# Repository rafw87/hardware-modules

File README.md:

# Various hardware modules

## [esp-prog-adapter](esp-prog-adapter)

Simple adapter allowing to connect [ESP-PROG board](https://docs.espressif.com/projects/espressif-esp-iot-solution/en/latest/hw-reference/ESP-Prog_guide.html)
to breadboard, using provided IDC cables (1.27mm pitch).

## [ESP-32 board on Arduino footprint](modules/esp-32-board)

ESP-WROOM-32 (or ESP32-SOLO-1) development kit with Micro-USB port, DC Input and ESP-PROG interface,
based on Arduino footprint.

## [NE555 Astable Circuit Breadboard Adapter](modules/ne555-astable-adapter)

This adapter implements common wiring for NE555 astable circuit, exposing pins for external R1, R2 and C1, and of course for VCC, GND and output.

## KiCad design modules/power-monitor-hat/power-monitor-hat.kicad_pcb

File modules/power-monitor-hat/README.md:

# Power monitor HAT

Turns your Raspberry PI into 3-channel voltage and current monitor for other devices.

## Features
 - 3 separate channels, each with own INA219 chip and shunt resistor (see below for resistor selection)
 - Different possible power sources (controlled by jumpers):
   - external (separate input for each channel), provided on screw terminal,
   - internal 5V from common DC input
     - may be shorted to Raspberry's 5V pin using solderjumper on the bottom or left as separate circuit,
   - internal 3.3V - powered from 5V using internal LDO regulator
 - Fuse and an "ideal diode" circuit protecting DC source when shorted.
 - 4 LEDs:
   - PWR (connected to 5V bus)
   - 3 LEDs, one for each channel, connected to selected channel's power source
 - Header for UART - to communicate with measured device
 - Test points for I2C
 - Standard ID EEPROM from [hat specification](https://github.com/raspberrypi/hats)
 
## Devices list

### I2C
 Address | Device   | Description 
:-------:|:--------:|:-----------:
|  0x40  |  INA219  | Channel 1  
|  0x41  |  INA219  | Channel 2  
|  0x42  |  INA219  | Channel 3  

## Shunt resistor selection

Equations and tables below may help to select proper shunt resistor according to needs.

### Current

$R_{shunt}$ | Absolute maximum current* | Maximum measurable current** | Maximum recommended current**
:----------:|:-------------------------:|:----------------------------:|:-----------------------------:
|  0.1Ω     | 2.73A / 3.16A             | 3.20A                        | 0.40A
|  0.2Ω     | 1.93A / 2.23A               | 1.60A                        | 0.20A
|  0.5Ω     | 1.22A / 1.41A               | 0.64A                        | 0.08A
|  1.0Ω     | 0.86A / 1.00A               | 0.32A                        | 0.04A

\* Maximum allowed current for (respecively) 0.75W and 1W rated resistor of given resistance. Remember to include some margin for safety purpose. Equation:
  $$I = \sqrt{P_{max} \over R_{shunt}}$$

\** Maximum measurable ( $PGA = /8$, $V_{pga} = \pm 320mV$ ) and recommended ( $PGA = 1$, $V_{pga} = \pm 40mV$ ) current for given resistor. Equation:
  $$I = {V_{pga} \over R_{shunt}}$$

### Voltage drop

$R_{shunt}$       | 0.1A  | 0.2A  | 0.5A  | 1A     | 2A
:----------------:|:-----:|:-----:|:-----:|:------:|:----:
|  0.1Ω           | 0.01V | 0.02V | 0.05V | 0.10V  | 0.20V
|  0.2Ω           | 0.02V | 0.04V | 0.10V | 0.20V  | 0.40V
|  0.5Ω           | 0.05V | 0.10V | 0.25V | 0.50V  | 1.00V
|  1.0Ω           | 0.10V | 0.20V | 0.50V | 1.00V  | 2.00V

Equation:
$$V_{shunt} = R_{shunt} * I$$

### Tolerance and temperature coefficient
Simple answer: less is better (but more expensive) :)

Depends on actual purpose of HAT and expected quality of measurements.

Current measurement tolerance is linear to resistor tolerance, so for 1% tolerance we can expect also 1% variation of current measurement.

Due of temperature coefficient, it's also recommended to not "stress" resistor close to its maximum power rating, causing excessive heating.
Some heat is unfortunately generated by RaspberryPI itself. If needed, it may be compensated programmatically (knowing temperature coefficient and actual temperature) or HAT may be connected using extension cable to not be affected by RPi's heat.

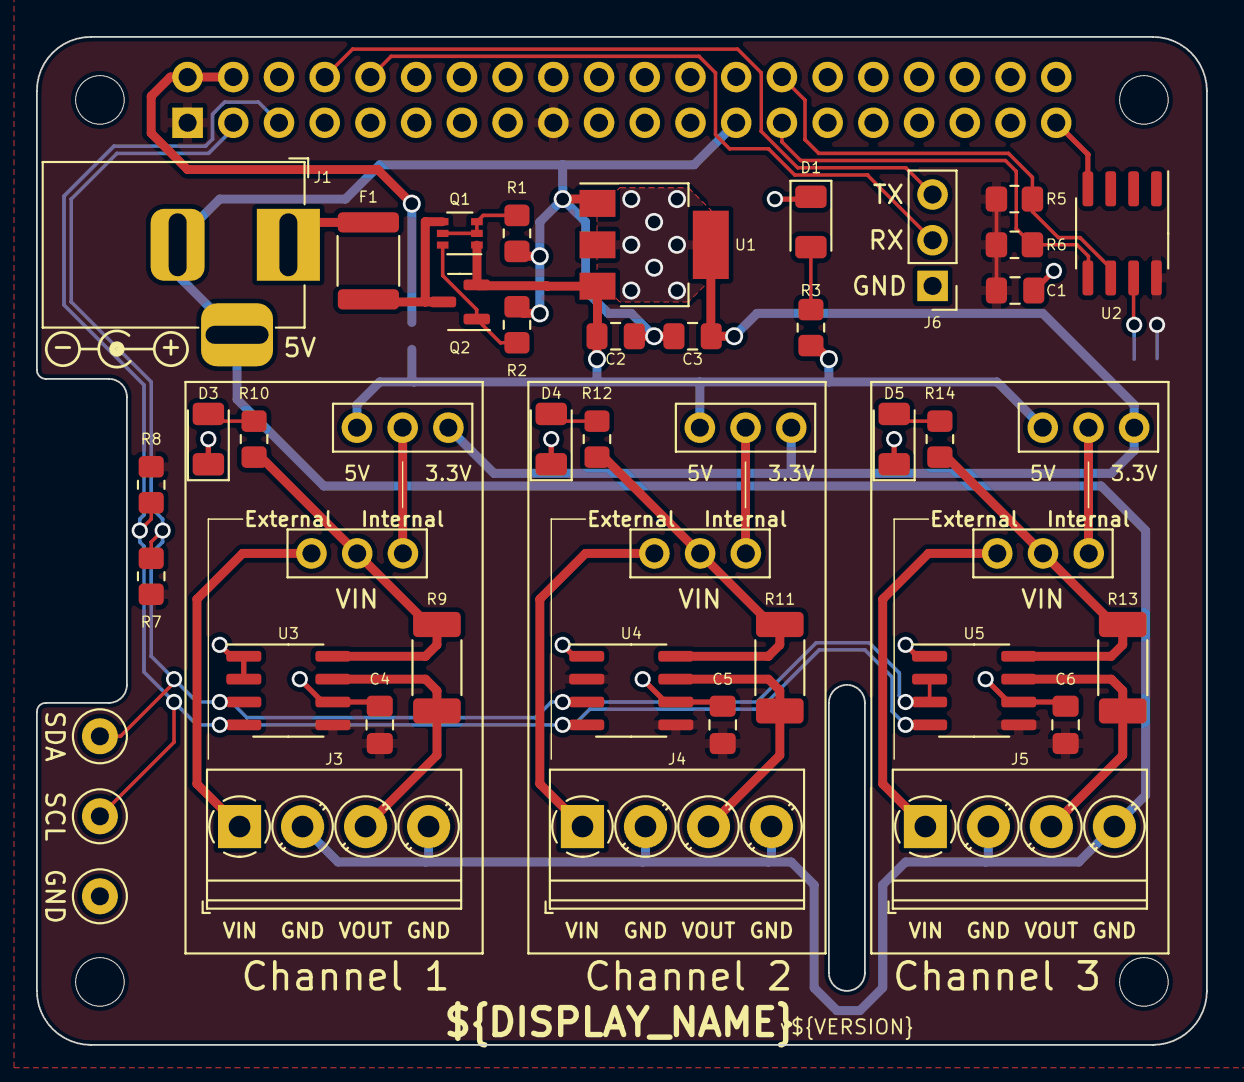
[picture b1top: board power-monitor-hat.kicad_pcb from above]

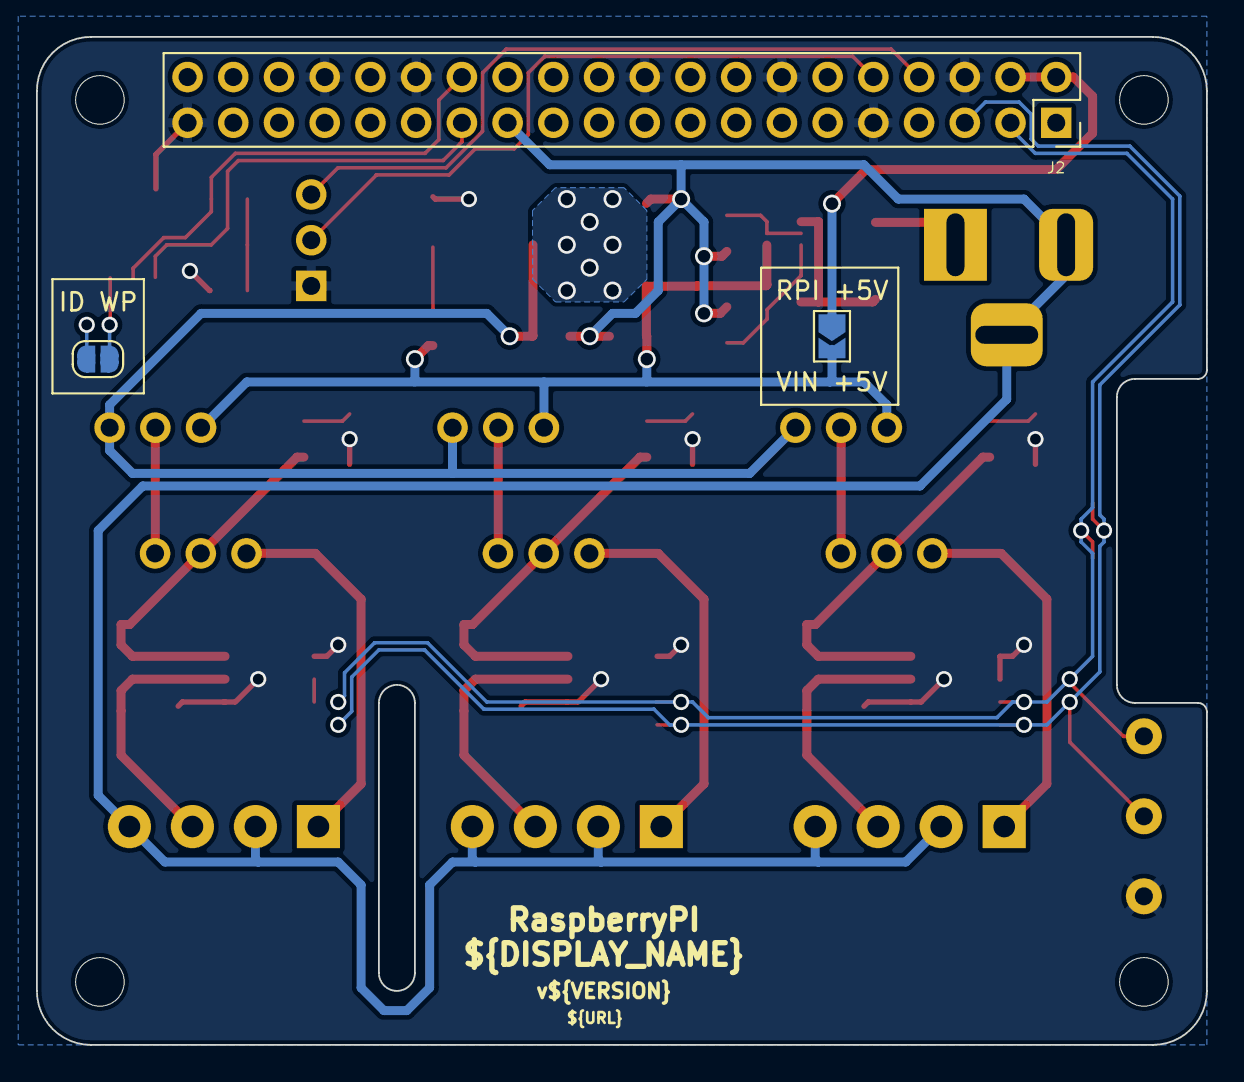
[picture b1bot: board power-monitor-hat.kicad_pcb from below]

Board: 2 copper layers, 65.0 x 56.0 mm, 53 parts (3 on the bottom side), 33 nets.

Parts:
C1, C4, C5, C6: 100n; C_0805_2012Metric_Pad1.18x1.45mm_HandSolder
C2, C3: 10u; C_0805_2012Metric_Pad1.18x1.45mm_HandSolder
D1, D3, D4, D5: LED; LED_1206_3216Metric
F1: MF-MSMF250/16X-2; Fuse_1812_4532Metric
J1: Barrel_Jack_Switch; BarrelJack_CLIFF_FC68148_Horizontal
J2: GPIO; PinSocket_2x20_P2.54mm_Vertical
J3, J4, J5: OutputTerminal; TerminalBlock_Phoenix_PT-1,5-4-3.5-H_1x04_P3.50mm_Horizontal
J6: Conn_01x03; PinHeader_1x03_P2.54mm_Vertical
JP1: 5V_Bridge; SolderJumper-2_P1.3mm_Open_TrianglePad1.0x1.5mm
JP2: ID_WP; SolderJumper-2_P1.3mm_Open_RoundedPad1.0x1.5mm
JP3, JP4, JP5, JP6, JP7, JP8: Jumper; PinHeader_1x03_P2.54mm_Vertical_NoFP
MH1, MH2, MH3, MH4: MountingHole_2.7mm_M2.5
Q1: BC856BDW1; SOT-363_SC-70-6
Q2: SI2301CDS; SOT-23
R1, R7, R8: 10k; R_0805_2012Metric_Pad1.20x1.40mm_HandSolder
R2: 47k; R_0805_2012Metric_Pad1.20x1.40mm_HandSolder
R3: 470R; R_0805_2012Metric_Pad1.20x1.40mm_HandSolder
R5, R6: 3.9k; R_0805_2012Metric_Pad1.20x1.40mm_HandSolder
R9, R11, R13: 0R5; R_2010_5025Metric_Pad1.40x2.65mm_HandSolder
R10, R12, R14: 2kR; R_0805_2012Metric_Pad1.20x1.40mm_HandSolder
SYM1: Symbol_Barrel_Polarity
TP1, TP2, TP3: TestPoint; TestPoint_Loop_D1.80mm_Drill1.0mm_Beaded
U1: NCP1117-3.3_SOT223; SOT-223-3_TabPin2
U2: CAT24C256; SOIC-8_3.9x4.9mm_P1.27mm
U3, U4, U5: INA219AxD; SOIC-8_3.9x4.9mm_P1.27mm

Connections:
+3.3V: C1.1, C4.1, C5.1, C6.1, J2.1 (3V3), J2.17 (3V3), JP2.2 (B), R5.1, R6.1, R7.1, R8.1, U2.8 (VCC), U3.5 (VS), U4.2 (A0), U4.5 (VS), U5.5 (VS)
+3.3VP: C3.1, JP4.3 (B), JP6.3 (B), JP8.3 (B), U1.2 (VO)
+5V: J2.2 (5V), J2.4 (5V), JP1.1 (A)
+5VP: C2.1, JP1.2 (B), JP4.1 (A), JP6.1 (A), JP8.1 (A), Q1.1 (E1), Q2.2 (S), R3.2, U1.3 (VI)
/ID_SCL: J2.28 (ID_SC/GPIO1), R5.2, U2.6 (SCL)
/ID_SDA: J2.27 (ID_SD/GPIO0), R6.2, U2.5 (SDA)
/PowerChannel 1/EXTERNAL_VIN: J3.1, JP3.1 (A)
/PowerChannel 1/INTERNAL_VIN: JP3.3 (B), JP4.2 (C)
/PowerChannel 1/VIN: JP3.2 (C), R9.1, R10.2, U3.8 (IN+)
/PowerChannel 1/VOUT: J3.3, R9.2, U3.7 (IN-)
/PowerChannel 2/EXTERNAL_VIN: J4.1, JP5.1 (A)
/PowerChannel 2/INTERNAL_VIN: JP5.3 (B), JP6.2 (C)
/PowerChannel 2/VIN: JP5.2 (C), R11.1, R12.2, U4.8 (IN+)
/PowerChannel 2/VOUT: J4.3, R11.2, U4.7 (IN-)
/PowerChannel 3/EXTERNAL_VIN: J5.1, JP7.1 (A)
/PowerChannel 3/INTERNAL_VIN: JP7.3 (B), JP8.2 (C)
/PowerChannel 3/VIN: JP7.2 (C), R13.1, R14.2, U5.8 (IN+)
/PowerChannel 3/VOUT: J5.3, R13.2, U5.7 (IN-)
/RX: J2.10 (GPIO15/RXD), J6.2
/SCL: J2.5 (SCL/GPIO3), R8.2, TP3.1, U3.4 (SCL), U4.4 (SCL), U5.4 (SCL)
/SDA: J2.3 (SDA/GPIO2), R7.2, TP2.1, U3.3 (SDA), U4.3 (SDA), U5.2 (A0), U5.3 (SDA)
/TX: J2.8 (GPIO14/TXD), J6.3
/Vfused: F1.2, Q1.4 (E2), Q2.3 (D)
/Vpsu: F1.1, J1.1
GND: C1.2, C4.2, C5.2, C6.2, D1.1 (K), D3.1 (K), D4.1 (K), D5.1 (K), J2.6 (GND), J2.9 (GND), J2.14 (GND), J2.20 (GND), J2.30 (GND), J2.34 (GND), J2.39 (GND), J6.1, TP1.1, U2.4 (GND), U3.1 (A1), U3.2 (A0), U3.6 (GND), U4.1 (A1), U4.6 (GND), U5.1 (A1), U5.6 (GND)
GNDPWR: C2.2, C3.2, J1.2, J1.3, J2.25 (GND), J3.2, J3.4, J4.2, J4.4, J5.2, J5.4, R1.2, R2.2, U1.1 (GND)
unnamed: D1.2 (A), R3.1
unnamed: JP2.1 (A), U2.7 (WP)
unnamed: Q1.2 (B1), Q1.3 (C2), Q1.5 (B2), R1.1
unnamed: Q1.6 (C1), Q2.1 (G), R2.1
unnamed: D3.2 (A), R10.1
unnamed: D4.2 (A), R12.1
unnamed: D5.2 (A), R14.1

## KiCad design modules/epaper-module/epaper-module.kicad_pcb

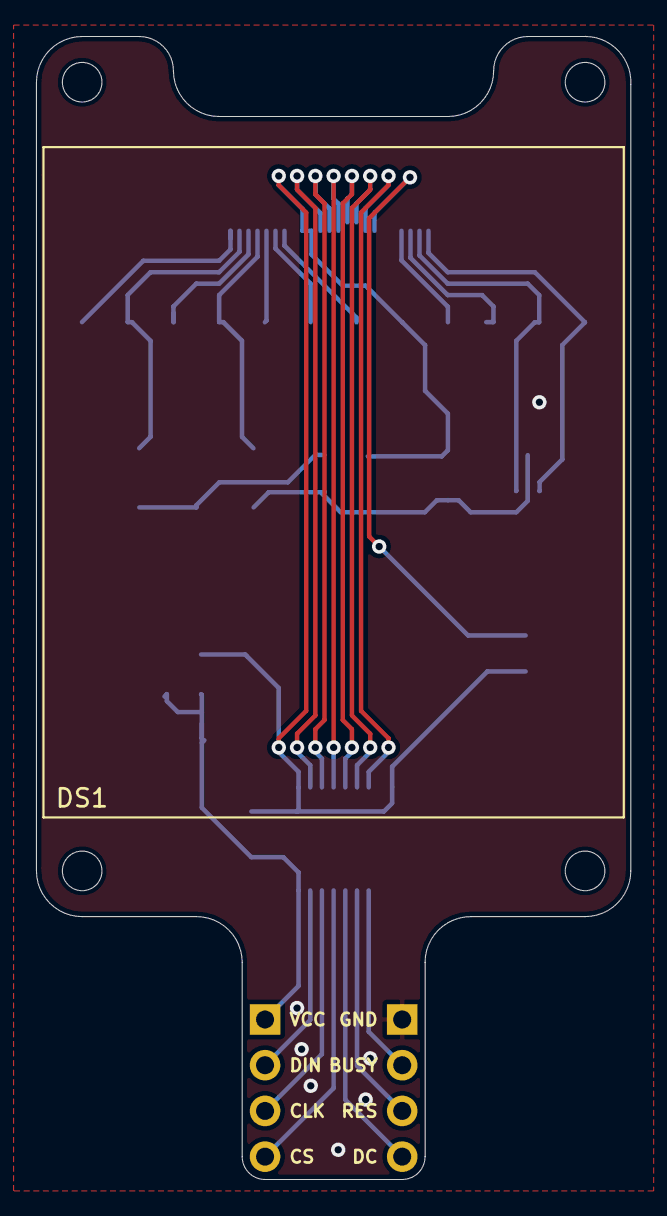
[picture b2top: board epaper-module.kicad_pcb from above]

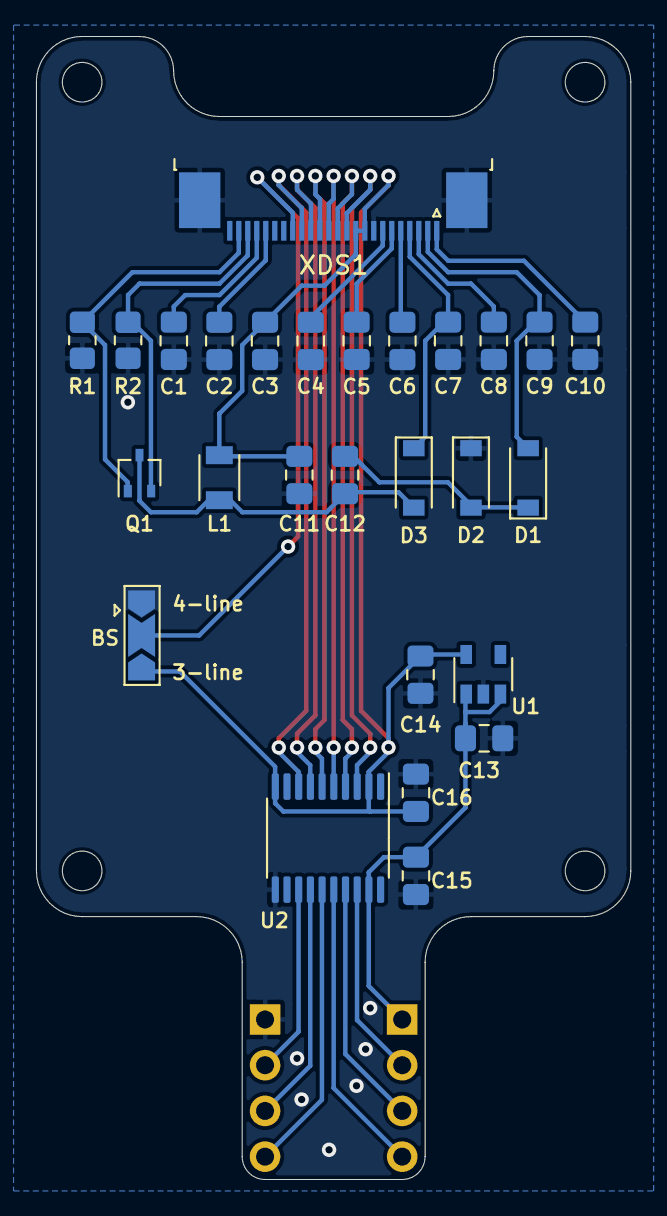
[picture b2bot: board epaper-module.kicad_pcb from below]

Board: 2 copper layers, 33.0 x 63.5 mm, 34 parts (29 on the bottom side), 29 nets.

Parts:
C1, C2, C3, C4, C5, C6, C7, C8, C9, C10: 1uF; C_0805_2012Metric_Pad1.18x1.45mm_HandSolder
C11, C12, C14: 4.7uF; C_0805_2012Metric_Pad1.18x1.45mm_HandSolder
C13: 10uF; C_0805_2012Metric_Pad1.18x1.45mm_HandSolder
C15, C16: 100nF; C_0805_2012Metric_Pad1.18x1.45mm_HandSolder
D1, D2, D3: MBR0530; D_SOD-123
DS1: WSH-12561
H1, H2, H3, H4: MountingHole; MountingHole_2.2mm_M2
J1, J2: Conn_01x04; PinHeader_1x04_P2.54mm_Vertical
JP1: Jumper_NC_Dual; SolderJumper-3_P2.0mm_Open_TrianglePad1.0x1.5mm
L1: 10uH; L_TDK_NLV25_2.5x2.0mm
Q1: Si1308EDL; SOT-323_SC-70
R1: 10k; R_0805_2012Metric_Pad1.20x1.40mm_HandSolder
R2: 3 Ohm; R_0805_2012Metric_Pad1.20x1.40mm_HandSolder
U1: MIC5504-3.3YM5; SOT-23-5
U2: TXS0108EPW; TSSOP-20_4.4x6.5mm_P0.65mm
XDS1: WSH-12561-FFC-MP; TE_2-1734839-4_1x24-1MP_P0.5mm_Horizontal

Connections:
+3V3: C3.1, C11.1, C14.1, C16.1, JP1.3, L1.2, U1.5, U2.2, U2.10, XDS1.9, XDS1.10
/BS: JP1.2, XDS1.17
/BUSY: J1.2, U2.13
/BUSY': U2.8, XDS1.16
/CLK: J2.3, U2.17
/CLK': U2.4, XDS1.12
/CS: J2.4, U2.16
/CS': U2.5, XDS1.13
/DC: J1.4, U2.15
/DC': U2.6, XDS1.14
/DIN: J2.2, U2.18
/DIN': U2.3, XDS1.11
/GDR: Q1.1, R1.1, XDS1.23
/PREVGH: C7.1, D3.1, XDS1.4
/PREVGL: C9.1, D1.2, XDS1.2
/RES: J1.3, U2.14
/RES': U2.7, XDS1.15
/RESE: Q1.2, R2.1, XDS1.22
/VCOM: C10.1, XDS1.1
/VDD: C4.1, XDS1.7
/VSH1: C6.1, XDS1.5
/VSH2: C2.1, XDS1.20
/VSL: C8.1, XDS1.3
GND: C1.2, C2.2, C3.2, C4.2, C5.2, C6.2, C7.2, C8.2, C9.2, C10.2, C11.2, C13.2, C14.2, C15.2, C16.2, D2.1, J1.1, JP1.1, R1.2, R2.2, U1.2, U2.11, XDS1.8, XDS1.MP
unnamed: C1.1, XDS1.21
unnamed: C5.1, XDS1.6
unnamed: C12.1, D1.1, D2.2
unnamed: C12.2, D3.2, L1.1, Q1.3
VCC: C13.1, C15.1, J2.1, U1.1, U1.3, U2.19

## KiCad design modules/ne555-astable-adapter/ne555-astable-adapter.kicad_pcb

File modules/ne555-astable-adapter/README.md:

# NE555 Astable Circuit Breadboard Adapter

## Story
OK, so you want to build a timer, emiting pulses with given interval on breadboard using NE555. Easy, right?
All you need is to put your NE555 in the middle and implement astable circuit around it, like this:

Looks easy? Only on the schematic :wink:
- Trigger and Treshold should be connected, but are on the opposite side, so single jumper is not an option.
  What is the shortest wire you have? :)
- R2 should connect pin 7 either with pin 2 (over IC?) or with pin 6 (requires vertical resistor).
- You need power and ground on both sides.
- Quickly you have no idea which pins are connected without looking into schematic :wink:

Finally you ends with something like this:

Maybe is there any easier way? :thinking: Maybe some adapter?

## Adapter

This adapter implements common wiring for NE555 astable circuit, exposing pins for external R1, R2 and C1,
and of course for VCC, GND and output. Additionally exposes pin for Control, but allows also to solder fixed C2 capacitor.
Some pins are duplicated, making it easier to connect and allowing to choose most comfortable pitch.

Comparison:

- Trigger and Treshold are internally connected and exposed as TRI
- Distance between R2 terminals can be 7.62mm, 10.16mm or 12.7mm (3, 4 or 5 holes on breadboard) making it easy to connect
  with horizontal resistor
- It's possible to connect to VCC/GND only from one side (as above)
- Pins are labelled

Adapter from top:

## Resources
- [Schematic](docs/ne555-astable-adapter-schematic.pdf?raw=true)
- [BOM](https://htmlpreview.github.io/?https://raw.githubusercontent.com/rafw87/hardware-modules/master/modules/ne555-astable-adapter/docs/ne555-astable-adapter-bom.html)
- [Project on PCBWay](https://www.pcbway.com/project/shareproject/NE555_Astable_Circuit_Breadboard_Adapter.html)
- Gerbers
  - [PCBWay](docs/gerbers/ne555-astable-adapter-PCBWay.zip?raw=true)

## License
<br />This work is licensed under a <a rel="license" href="http://creativecommons.org/licenses/by-sa/4.0/">Creative Commons Attribution-ShareAlike 4.0 International License</a>.

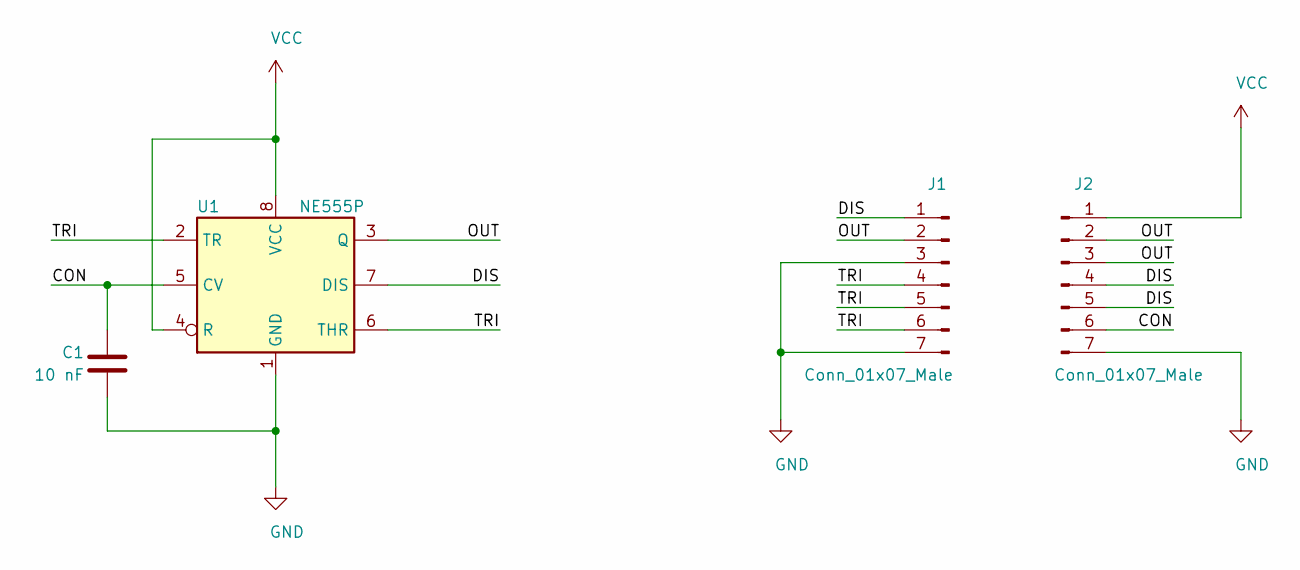
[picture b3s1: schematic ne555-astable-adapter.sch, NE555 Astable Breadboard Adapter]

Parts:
C1: 10 nF; C_Disc_D3.0mm_W1.6mm_P2.50mm
J1, J2: Conn_01x07_Male; PinHeader_1x07_P2.54mm_Vertical
U1: NE555P; DIP-8_W7.62mm

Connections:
/CON: C1.1, J2.6, U1.5 (CV)
/DIS: J1.1, J2.4, J2.5, U1.7 (DIS)
/OUT: J1.2, J2.2, J2.3, U1.3 (Q)
/TRI: J1.4, J1.5, J1.6, U1.2 (TR), U1.6 (THR)
GND: C1.2, J1.3, J1.7, J2.7, U1.1 (GND)
VCC: J2.1, U1.4 (R), U1.8 (VCC)

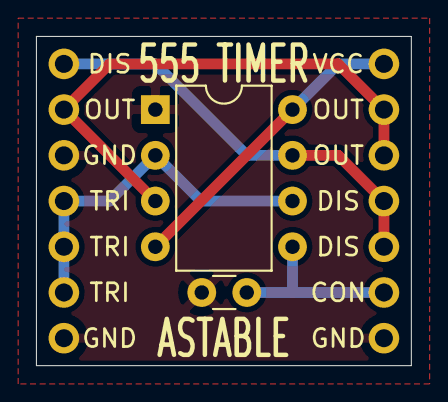
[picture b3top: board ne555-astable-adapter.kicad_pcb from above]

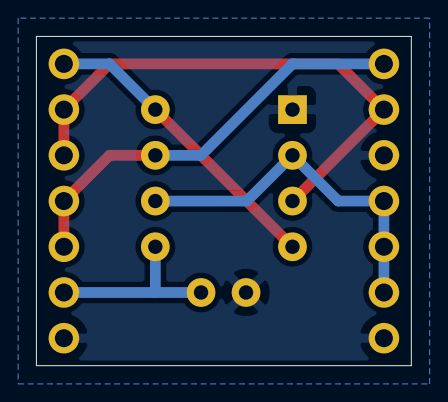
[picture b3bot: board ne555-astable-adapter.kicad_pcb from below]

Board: 2 copper layers, 20.8 x 18.3 mm, 4 parts (2 on the bottom side), 6 nets.

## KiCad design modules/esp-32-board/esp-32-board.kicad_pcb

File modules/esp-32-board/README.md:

# ESP-32 board on Arduino footprint

ESP-WROOM-32 (or ESP32-SOLO-1) development kit with Micro-USB port, DC Input and ESP-PROG interface.

Based on Arduino Uno/Leonardo footprint, so (apart from interesting appearance)
allows to use stands and (partially) enclosures from original Arduino.

**Note:** It's not an Arduino clone, so it's not compatible (neither electrically nor physically) with Arduino shields.
Functionally it's evaluation board like ESP32-DevKitC.

## Resources
- [Schematic](docs/esp-32-board-schematic.pdf?raw=true)
- [BOM](https://htmlpreview.github.io/?https://raw.githubusercontent.com/rafw87/hardware-modules/master/modules/esp-32-board/docs/esp-32-board-bom.html)
- [Project on PCBWay](https://www.pcbway.com/project/shareproject/ESP_32_board_on_Arduino_footprint.html)
- Gerbers
  - [PCBWay](docs/gerbers/esp-32-board-PCBWay.zip?raw=true)

## License
<br />This work is licensed under a <a rel="license" href="http://creativecommons.org/licenses/by-sa/4.0/">Creative Commons Attribution-ShareAlike 4.0 International License</a>.

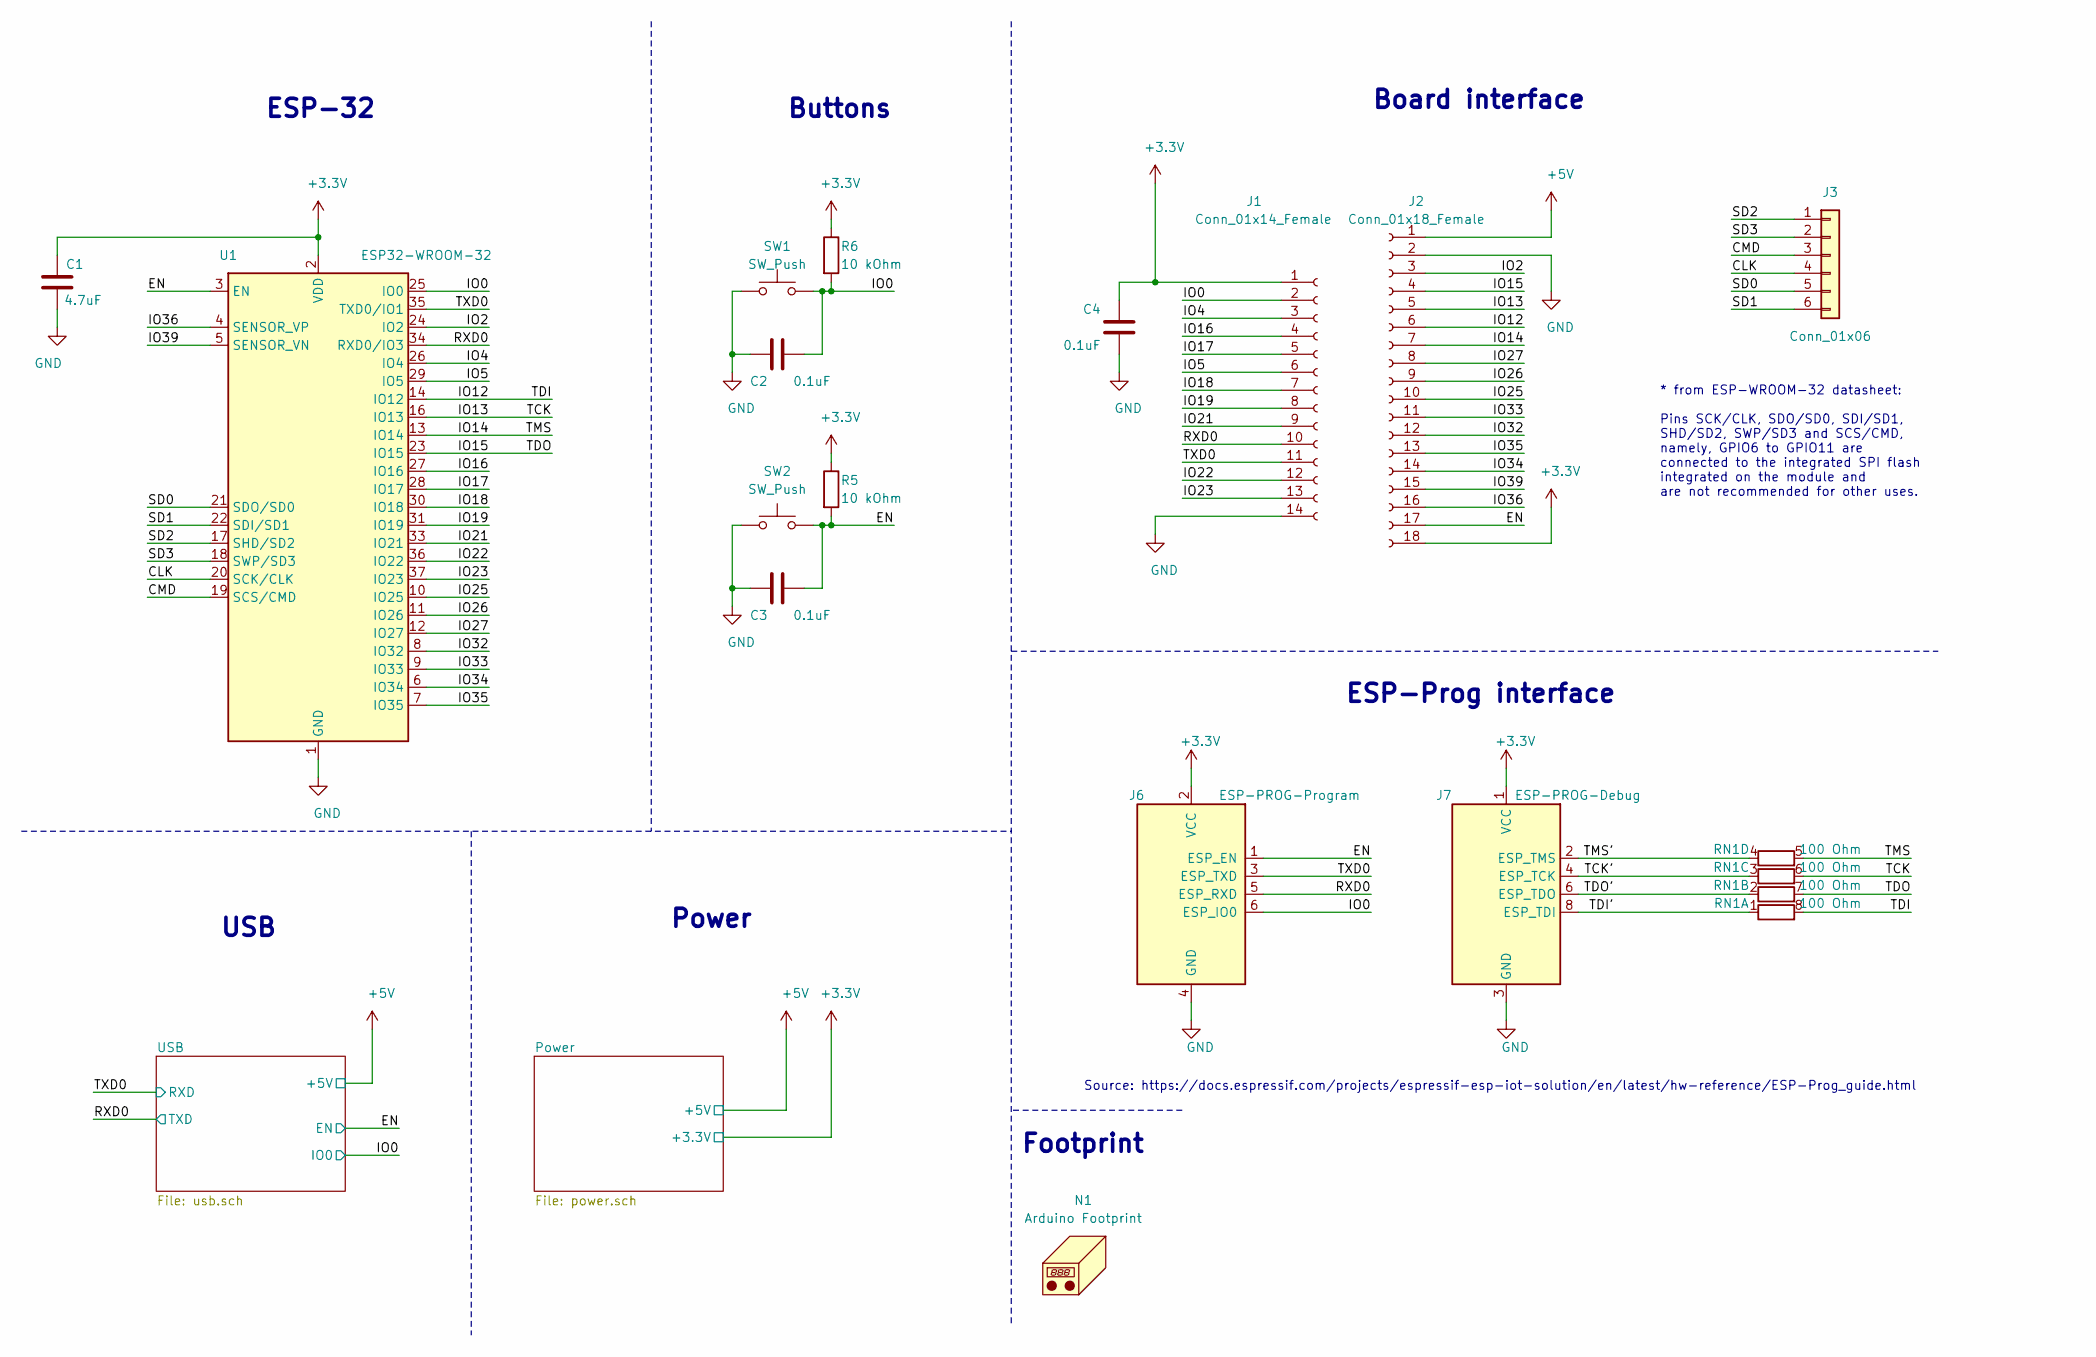
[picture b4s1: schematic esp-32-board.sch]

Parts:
C1: 4.7uF; C_0805_2012Metric_Pad1.18x1.45mm_HandSolder
C2, C3, C4: 0.1uF; C_0805_2012Metric_Pad1.18x1.45mm_HandSolder
J1: Conn_01x14_Female; PinSocket_1x14_P2.54mm_Vertical
J2: Conn_01x18_Female; PinSocket_1x18_P2.54mm_Vertical
J3: Conn_01x06; PinSocket_1x06_P2.54mm_Vertical
J6: ESP-PROG-Program; IDC-Header_2x03_P1.27mm_Vertical_SMD
J7: ESP-PROG-Debug; IDC-Header_2x05_P1.27mm_Vertical_SMD
N1: Arduino Footprint; ArduinoFootprint
R5, R6: 10 kOhm; R_0805_2012Metric_Pad1.20x1.40mm_HandSolder
RN1: 100 Ohm; R_Array_Convex_4x0612
SW1, SW2: SW_Push; SW_Push_1P1T_NO_6x6mm_H4.3mm
U1: ESP32-WROOM-32; ESP32-WROOM-32-ThermalVias

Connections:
+3V3: C1.1, C4.1, J1.1, J2.18, J6.2 (VCC), J7.1 (VCC), R5.1, R6.1, U1.2 (VDD); also elsewhere on the board
+5V: J2.1; also elsewhere on the board
/CLK: J3.4, U1.20 (SCK/CLK)
/CMD: J3.3, U1.19 (SCS/CMD)
/EN: C3.2, J2.17, J6.1 (ESP_EN), R5.2, SW2.2, U1.3 (EN); also elsewhere on the board
/IO0: C2.2, J1.2, J6.6 (ESP_IO0), R6.2, SW1.2, U1.25 (IO0); also elsewhere on the board
/IO2: J2.3, U1.24 (IO2)
/IO4: J1.3, U1.26 (IO4)
/IO5: J1.6, U1.29 (IO5)
/IO12: J2.6, RN1.8 (R1.2), U1.14 (IO12)
/IO13: J2.5, RN1.6 (R3.2), U1.16 (IO13)
/IO14: J2.7, RN1.5 (R4.2), U1.13 (IO14)
/IO15: J2.4, RN1.7 (R2.2), U1.23 (IO15)
/IO16: J1.4, U1.27 (IO16)
/IO17: J1.5, U1.28 (IO17)
/IO18: J1.7, U1.30 (IO18)
/IO19: J1.8, U1.31 (IO19)
/IO21: J1.9, U1.33 (IO21)
/IO22: J1.12, U1.36 (IO22)
/IO23: J1.13, U1.37 (IO23)
/IO25: J2.10, U1.10 (IO25)
/IO26: J2.9, U1.11 (IO26)
/IO27: J2.8, U1.12 (IO27)
/IO32: J2.12, U1.8 (IO32)
/IO33: J2.11, U1.9 (IO33)
/IO34: J2.14, U1.6 (IO34)
/IO35: J2.13, U1.7 (IO35)
/IO36: J2.16, U1.4 (SENSOR_VP)
/IO39: J2.15, U1.5 (SENSOR_VN)
/RXD0: J1.10, J6.5 (ESP_RXD), U1.34 (RXD0/IO3); also elsewhere on the board
/SD0: J3.5, U1.21 (SDO/SD0)
/SD1: J3.6, U1.22 (SDI/SD1)
/SD2: J3.1, U1.17 (SHD/SD2)
/SD3: J3.2, U1.18 (SWP/SD3)
/TCK': J7.4 (ESP_TCK), RN1.3 (R3.1)
/TDI': J7.8 (ESP_TDI), RN1.1 (R1.1)
/TDO': J7.6 (ESP_TDO), RN1.2 (R2.1)
/TMS': J7.2 (ESP_TMS), RN1.4 (R4.1)
/TXD0: J1.11, J6.3 (ESP_TXD), U1.35 (TXD0/IO1); also elsewhere on the board
GND: C1.2, C2.1, C3.1, C4.2, J1.14, J2.2, J6.4 (GND), J7.3 (GND), J7.5 (GND), J7.7 (GND), J7.9 (GND), SW1.1, SW2.1, U1.1 (GND), U1.15 (GND), U1.38 (GND), U1.39 (GND); also elsewhere on the board

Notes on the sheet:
Power
ESP-Prog interface
Board interface
ESP-32
Buttons
USB
Footprint
* from ESP-WROOM-32 datasheet: Pins SCK/CLK, SDO/SD0, SDI/SD1, SHD/SD2, SWP/SD3 and SCS/CMD, namely, GPIO6 to GPIO11 are connected to the integrated SPI flash integrated on the module and are not recommended for other uses.
Source: https://docs.espressif.com/projects/espressif-esp-iot-solution/en/latest/hw-reference/ESP-Prog_guide.html

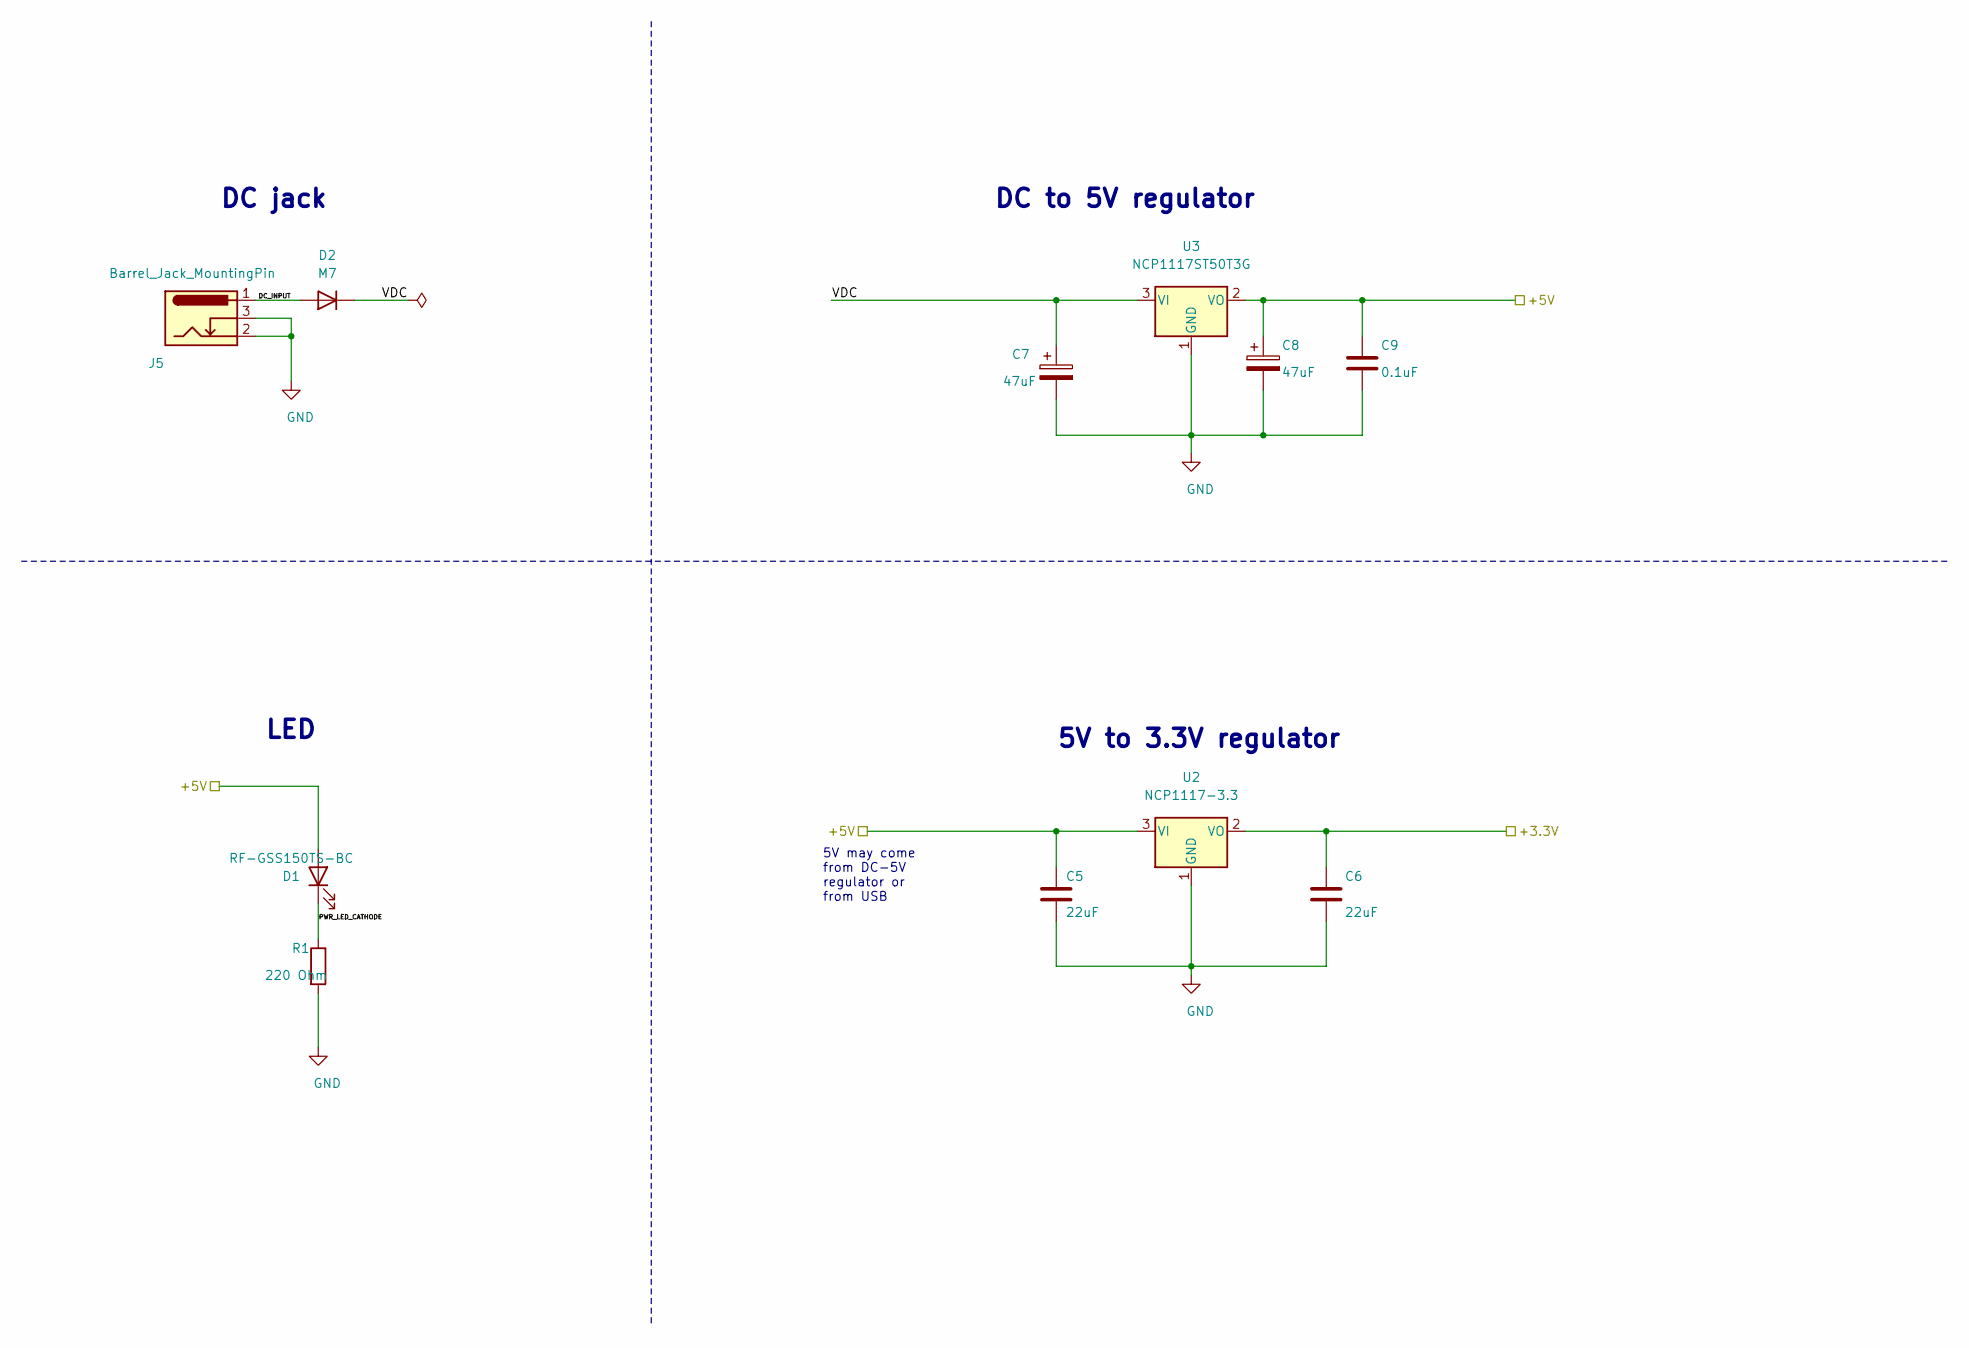
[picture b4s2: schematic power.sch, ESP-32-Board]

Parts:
C5, C6: 22uF; C_0805_2012Metric_Pad1.18x1.45mm_HandSolder
C7, C8: 47uF; CP_Elec_5x5.9
C9: 0.1uF; C_0805_2012Metric_Pad1.18x1.45mm_HandSolder
D1: RF-GSS150TS-BC; LED_1206_3216Metric_Pad1.42x1.75mm_HandSolder
D2: M7; D_SMA_Handsoldering
J5: Barrel_Jack_MountingPin; BarrelJack_CLIFF_FC68148_Horizontal
R1: 220 Ohm; R_0805_2012Metric_Pad1.20x1.40mm_HandSolder
U2: NCP1117-3.3; SOT-223-3_TabPin2
U3: NCP1117ST50T3G; SOT-223-3_TabPin2

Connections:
+3V3: C6.1, U2.2 (VO); also elsewhere on the board
+5V: C5.1, C8.1, C9.1, D1.2 (A), U2.3 (VI), U3.2 (VO); also elsewhere on the board
/Power/DC_INPUT: D2.2 (A), J5.1
/Power/PWR_LED_CATHODE: D1.1 (K), R1.1
/Power/VDC: C7.1, D2.1 (K), U3.3 (VI)
GND: C5.2, C6.2, C7.2, C8.2, C9.2, J5.2, J5.3, R1.2, U2.1 (GND), U3.1 (GND); also elsewhere on the board

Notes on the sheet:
DC jack
DC to 5V regulator
5V to 3.3V regulator
5V may come from DC-5V regulator or from USB
LED

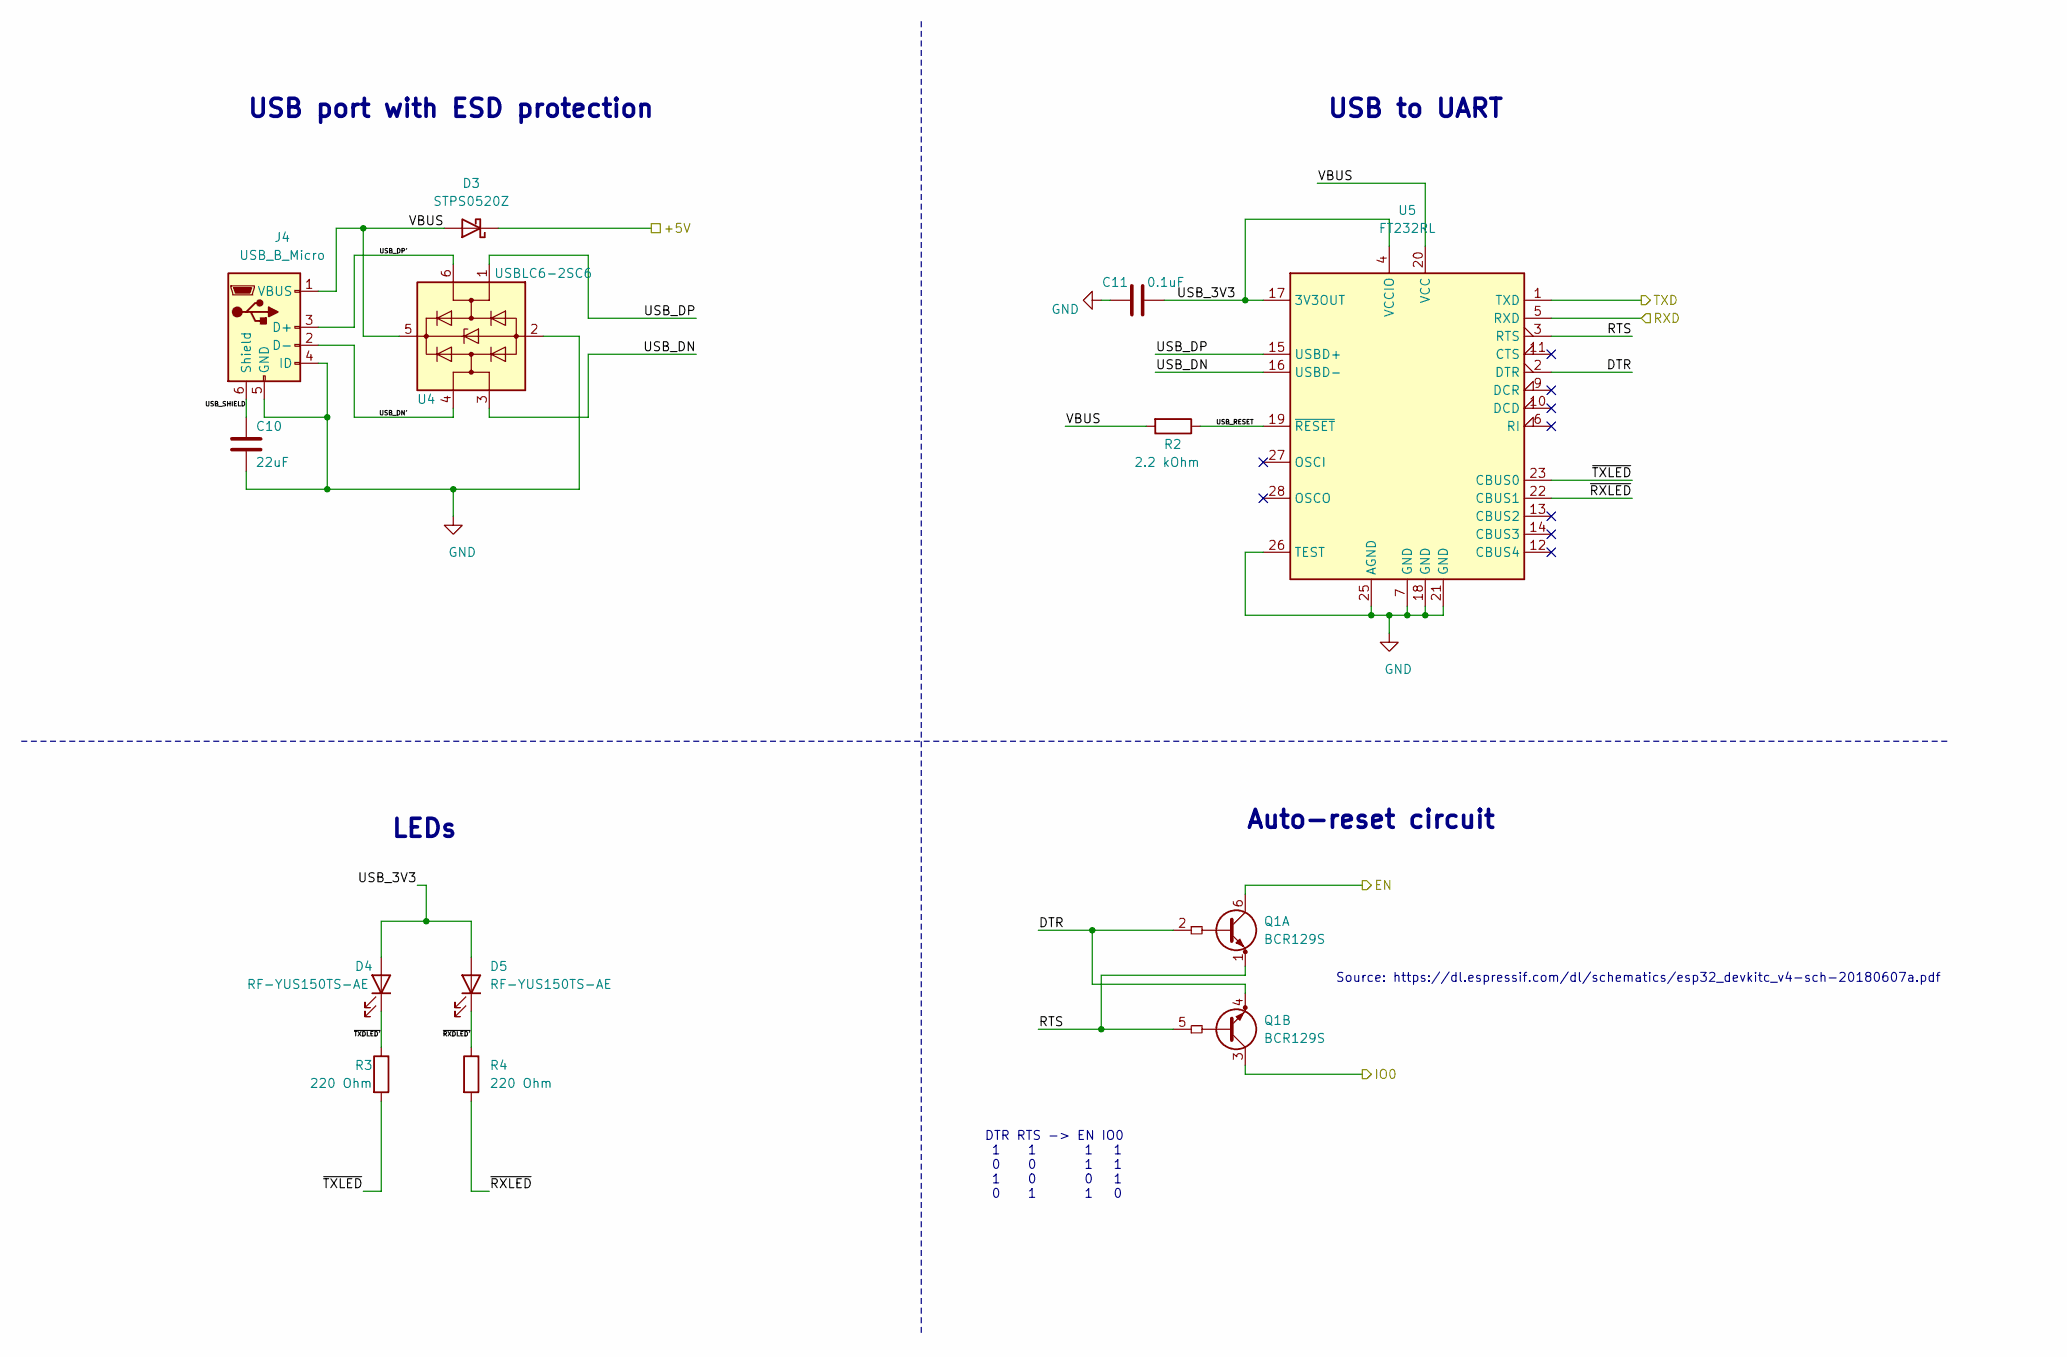
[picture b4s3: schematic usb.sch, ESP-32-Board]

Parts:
C10: 22uF; C_0805_2012Metric_Pad1.18x1.45mm_HandSolder
C11: 0.1uF; C_0805_2012Metric_Pad1.18x1.45mm_HandSolder
D3: STPS0520Z; D_SOD-123
D4, D5: RF-YUS150TS-AE; LED_1206_3216Metric_Pad1.42x1.75mm_HandSolder
J4: USB_B_Micro; USB_Micro-B_Amphenol_10118194_Horizontal
Q1: BCR129S; SOT-363_SC-70-6
R2: 2.2 kOhm; R_0805_2012Metric_Pad1.20x1.40mm_HandSolder
R3, R4: 220 Ohm; R_0805_2012Metric_Pad1.20x1.40mm_HandSolder
U4: USBLC6-2SC6; SOT-23-6
U5: FT232RL; SSOP-28_5.3x10.2mm_P0.65mm

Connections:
+5V: D3.1 (K); also elsewhere on the board
/EN: Q1.6 (C1); also elsewhere on the board
/IO0: Q1.3 (C1); also elsewhere on the board
/RXD0: U5.1 (TXD); also elsewhere on the board
/TXD0: U5.5 (RXD); also elsewhere on the board
/USB/DTR: Q1.2 (B1), Q1.4 (E2), U5.2 (DTR)
/USB/RTS: Q1.1 (E1), Q1.5 (B2), U5.3 (RTS)
/USB/USB_3V3: C11.1, D4.2 (A), D5.2 (A), U5.4 (VCCIO), U5.17 (3V3OUT)
/USB/USB_DN: U4.3 (I/O2), U5.16 (USBD-)
/USB/USB_DN': J4.2 (D-), U4.4 (I/O2)
/USB/USB_DP: U4.1 (I/O1), U5.15 (USBD+)
/USB/USB_DP': J4.3 (D+), U4.6 (I/O1)
/USB/USB_RESET: R2.1, U5.19 (~RESET~)
/USB/USB_SHIELD: C10.1, J4.6 (Shield)
/USB/VBUS: D3.2 (A), J4.1 (VBUS), R2.2, U4.5 (VBUS), U5.20 (VCC)
/USB/~RXDLED': D5.1 (K), R4.1
/USB/~RXLED: R4.2, U5.22 (CBUS1)
/USB/~TXDLED': D4.1 (K), R3.1
/USB/~TXLED: R3.2, U5.23 (CBUS0)
GND: C10.2, C11.2, J4.4 (ID), J4.5 (GND), U4.2 (GND), U5.7 (GND), U5.18 (GND), U5.21 (GND), U5.25 (AGND), U5.26 (TEST); also elsewhere on the board

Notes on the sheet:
USB port with ESD protection
USB to UART
Auto-reset circuit
LEDs
Source: https://dl.espressif.com/dl/schematics/esp32_devkitc_v4-sch-20180607a.pdf
DTR RTS -> EN IO0 1 1 1 1 0 0 1 1 1 0 0 1 0 1 1 0
